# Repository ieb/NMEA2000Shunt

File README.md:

# Nmea2000 Battery Sensor.

Mk1 used the ADC on an Attiny3224. Fine for voltage but not really accurate enough for low levels of current on a 75mV 100A shunt. 

This version is built arround a INA219 which is far easier to use. It speaks CAN to communicate with a NMEA2000 bus.

A BLE version was created, but in the end I felt it was overcomplicated and would need to deep sleep to avoid draining the battery.

A Modbus version was also created, but since it adds annother bus I decided to rebuild as a NMEA2000 device using the SmallNMEA2000 library that was used in the CanPressure sensor and EngineManagement modules. Both have been in service for 2 years with no issues.

# megaTinyCore 

This code needs megaTiny core 2.6.4 to work as there are some timing bugs that cause it to fail with the default platform IO 2.5.11 version. Upgrading is a pain as it requires installing a custom package. Installs from github fail as the layout of the source repo is wrong and missing files. 

The hacky way is to install manually as its not possible to install from a git repo due to a bug in the pio code that parses versions numbers.

		cd ~/src
		git clone https://github.com/SpenceKonde/megaTinyCore.git
		cd megaTinyCore
		git co -b 2.6.4
		mkdir ~/.platformio/packages/framework-arduino-megaavr-megatinycore@2.6.4
		cd ~/.platformio/packages/framework-arduino-megaavr-megatinycore@2.6.4
		cat << EOF > .piopm
		{"type": "tool", "name": "framework-arduino-megaavr-megatinycore", "version": "2.6.4", "spec": {"owner": "platformio", "id": 11448, "name": "framework-arduino-megaavr-megatinycore", "requirements": null, "uri": null}}
		EOF
		cat << EOF > package.json
		{
		  "name": "framework-arduino-megaavr-megatinycore",
		  "version": "2.6.4",
		  "description": "Arduino Wiring-based Framework for Microchip tinyAVR 0-series and 1-series chips (megaTinyCore)",
		  "keywords": [
		    "framework",
		    "arduino",
		    "microchip",
		    "tinyAVR"
		  ],
		  "repository": {
		    "type": "git",
		    "url": "https://github.com/ieb/megaTinyCore"
		  }
		}
		EOF
		ln -s ~/megaTinyCore/megaavr/* .
		ln -s ~/megaTinyCore/ChangeLog.md .
		ln -s ~/megaTinyCore/Installation.md .
		ln -s ~/megaTinyCore/MakeUPDIProgrammer.md .
		ln -s ~/megaTinyCore/README.md .
		ln -s ~/megaTinyCore/Wiring.md .

# Oled display

There is a i2c header but at this time the oled display was removed as it served minimal purpose and consumes more current.

# LED status

normal operation is on for 250ms, off for 6s. Error states are indetified by a number of 250ms flashes followed by on for 3s off for 3s.

## Key

* ^ == short flash 
* -3s- == 3s on for 3s
* _3s_ off for 3s. 
* Cycle repeats after 6s

|   flashes   | condition                                   |
|-------------|---------------------------------------------|
| ^           | normal                                      |
| ^^ -3s-     | INA219 chip failure                         |
| ^^^ -s3-    | Can bus not connected or failing to respond |
| ^^^^^ -s3-  | Both Can and INA219 failing                 |

# ToDo

* [x] Basic implementation, with CAN.
* [x] Average current and voltage over time period, eg 30s
* [ ] Test CAN using a CandelLite adapter.
* [x] Calibrate NTC sensors.
* [x] ~~Add 1.3 inch Oled display~~
* [x] ~~Implement current monitoring with auto scaling for different ranges using features of the INA219~~ Limited benefit see p21 Table 7
* [ ] design and make box

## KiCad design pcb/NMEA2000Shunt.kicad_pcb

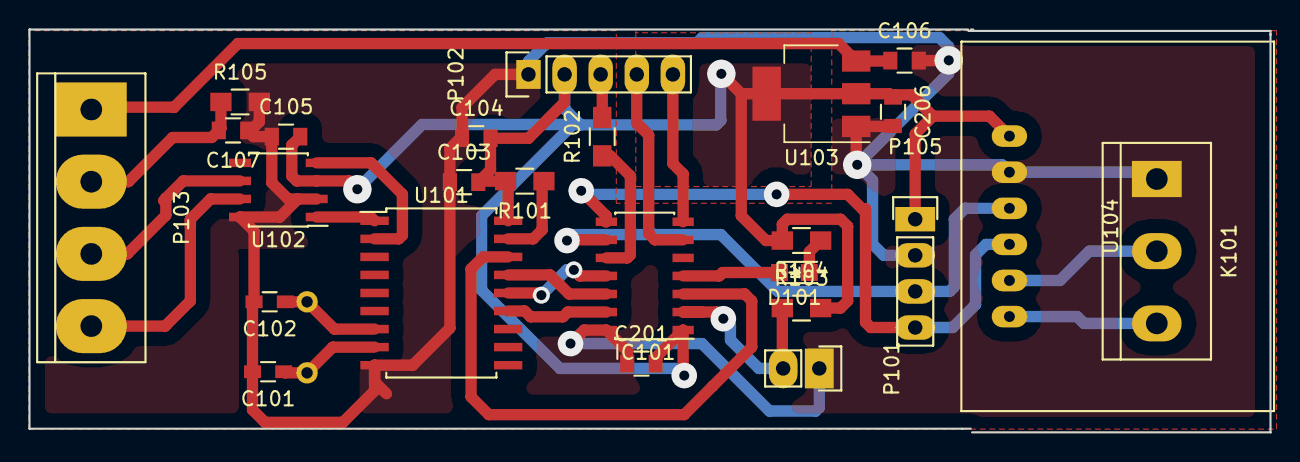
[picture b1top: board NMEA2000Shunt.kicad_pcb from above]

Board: 2 copper layers, 87.3 x 28.3 mm, 26 parts (1 on the bottom side), 26 nets.

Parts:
C101, C102: 22pF; R_0603_HandSoldering
C103, C106, C206: 10uF; C_0805
C104, C105, C107, C201: 100nF; C_0805
D101: LED; LED_0805
IC101: ATTINY3224-SS; SOIC-14_3.9x8.7mm_Pitch1.27mm
K101: Battery; bornier3
P101: Temp1; Pin_Header_Straight_1x02
P102: Prog; Pin_Header_Straight_1x05
P103: CAN; bornier4
P105: OLED; Pin_Header_Straight_1x04
R101, R103, R104, R105: 10K; R_0805_HandSoldering
R102: 270R; R_0805_HandSoldering
U101: MCP2515; SOIC-18W_7.5x11.6mm_Pitch1.27mm
U102: TJA1050; SOIC-8_3.9x4.9mm_Pitch1.27mm
U103: NCP1117ST50T3G; SOT-223-3Lead_TabPin2
U104: INA219-module; INA219Module
X101: 8MHz; Resonator-2pin_w10.0mm_h5.0mm

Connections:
5V: C103.2, C104.2, C105.2, C201.2, C206.1, IC101.1, P102.2, P105.1, R101.2, R103.2, R104.2, U101.18, U102.3, U103.2, U104.1
12v: C106.1, P103.1, U103.3
CANCS: IC101.3, U101.16
CANGND: C107.2, P103.2, R105.1
CANH: P103.4, U102.7
CANL: P103.3, U102.6
GND: C101.2, C102.2, C103.1, C104.1, C105.1, C106.2, C107.1, C201.1, C206.2, IC101.14, K101.1, P101.1, P102.1, P105.2, R105.2, U101.9, U102.2, U102.8, U103.1, U104.2
IN+: K101.3, U104.6
IN-: K101.2, U104.5
LED: D101.2, IC101.4
MISO: IC101.12, U101.15
MOSI: IC101.11, U101.14
unnamed: C101.1, U101.8, X101.1
unnamed: C102.1, U101.7, X101.2
unnamed: D101.1, R104.1
unnamed: P102.3, R102.2
unnamed: R101.1, U101.17
unnamed: U101.1, U102.1
unnamed: U101.2, U102.4
RX: IC101.6, P102.4
SCK: IC101.13, U101.13
SCL: IC101.9, P105.3, U104.3
SDA: IC101.8, P105.4, U104.4
TEMP1: IC101.2, P101.2, R103.1
TX: IC101.7, P102.5
UDPI: IC101.10, R102.1

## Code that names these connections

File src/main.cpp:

#include <Arduino.h>
#include <Wire.h>



#include "n2kshunt.h"
#include "commandline.h"
#include "ina219.h"
#include "config.h"
#include "ntcsensor.h"

// Hardware
// Vcc chip pin 1
#define TEMP1_PIN PIN_PA4 // chip pin 2
#define CANCS_PIN PIN_PA5 // chip pin 3
#define LED_PIN PIN_PA6 // chip pin 4
// PIN_PA7 not used       // chip pin 5
#define RX0_PIN   PIN_PB3 // chip pin 6, default
#define TX0_PIN   PIN_PB2 // chip pin 7, default
#define SDA_PIN   PIN_PB1 // chip pin 8, cant be moved.
#define SCL_PIN   PIN_PB0 // chip pin 9, cant be moved.
#define UDPI_PIN  PIN_PA0 // chip pin 10, cant be moved.
#define MOSI_PIN  PIN_PB1 // chip pin 11, default
#define MIS0_PIN  PIN_PB2 // chip pin 12, default
#define SCK_PIN   PIN_PB3 // chip pin 13, default
// GND chip pin 14

//  Check and update https://ieb.github.io/notes/ to get a clean address.
#define DEVICE_ADDRESS 26



// default serial for debug, serial 1 not used.
#define debug Serial


// configure CAN device
const SNMEA2000ProductInfo productInfomation PROGMEM={
                                       1300,                        // N2kVersion
                                       45,                         // Manufacturer's product code
                                       "Shunt",    // Manufacturer's Model ID
                                       "1.0.0.1 (2023-04-26)",     // Manufacturer's Software version code
                                       "1.0.0.2 (2023-04-26)",      // Manufacturer's Model version
                                       "0000003",                  // Manufacturer's Model serial code
                                       0,                           // SertificationLevel
                                       1                            // LoadEquivalency
};
const SNMEA2000ConfigInfo configInfo PROGMEM={
      "Battery Shunt",
      "Luna Technical Area",
      "https://github.com/ieb/NMEA2000Shunt"
};

uint8_t pgnEnableRegister = 0xff;


const unsigned long txPGN[] PROGMEM = { 
	127506L, // detailed DC status
	127513L, // battery configuration status
	127508L, // battery status message
    SNMEA200_DEFAULT_TX_PGN
};
const unsigned long rxPGN[] PROGMEM = { 
  SNMEA200_DEFAULT_RX_PGN
};

const SNMEA2000DeviceInfo devInfo = SNMEA2000DeviceInfo(
  02,   // device serial number
  170,  // Battery
  35    // Power
);



ConfigSettings settings;

Ina219 ina219(&debug);
CommandLine commandLine(&debug, &settings);
NtcSensor ntcSensor(&debug, TEMP1_PIN);


bool ina219Ok = false;
bool canOk = false;



N2kShunt n2kShunt = N2kShunt(DEVICE_ADDRESS, 
          &devInfo, 
          &productInfomation, 
          &configInfo, 
          &txPGN[0], 
          &rxPGN[0],
          CANCS_PIN
);
//          CANCS_PIN


void blink() {
	static unsigned long lastBlink = 0;
	static uint8_t led_state = 0;
	static unsigned long nextDelay = 3000;
	unsigned long now = millis();
	if ((now - lastBlink) > nextDelay ) {
		led_state = !led_state;
		digitalWrite(LED_PIN, led_state);
		if ( canOk && ina219Ok ) {
			if (!led_state) {
				// short bink dont block main thread.
				nextDelay = 250;
			} else {
				nextDelay = 6000;
			}
		} else if ( !led_state ) {
			nextDelay = 3000;
			// indicate a fault condition.
			// its ok to block the main thread as something is failing.
			// 3 flashes = can fail.
			// 2 flashes = ina219 fail.
			// 5 flashes == both failed.
			if (!canOk ) {
				for(int i = 0; i < 3; i++) {
					delay(250);
					digitalWrite(LED_PIN, HIGH);
					delay(250);
					digitalWrite(LED_PIN, LOW);
				}
			} 
			if (!ina219Ok) {
				for(int i = 0; i < 2; i++) {
					delay(250);
					digitalWrite(LED_PIN, HIGH);
					delay(250);
					digitalWrite(LED_PIN, LOW);
				}
			}
		    delay(250);
			digitalWrite(LED_PIN, HIGH);
		    delay(250);
			digitalWrite(LED_PIN, LOW);
		}
		lastBlink = millis();

	}

}



void readSensors() {
	debug.print(F(" v="));debug.print(ina219.getVoltage());
	debug.print(F(" mV c="));debug.print(ina219.getCurrent());
	double tempK = ntcSensor.getTemperature();
	debug.print(F(" A t="));debug.print(ntcSensor.getTemperature());
	debug.print(F(" K "));debug.print(ntcSensor.getTemperature()-273.15);
	debug.print(F(" C tons="));debug.print(millis());
	debug.println("");
}

void showStatus() {
	n2kShunt.dumpStatus();
}





void sendReading() {
	static unsigned long lastRead = 0;
	static uint8_t sid = 0;
	unsigned long now = millis();
	if ((now - lastRead) > 1500 ) {
		lastRead = now;
		sid++;
		double batteryTemperature = ntcSensor.getTemperature();
		double batteryVoltage = ina219.getVoltage();
		double batteryCurrent = ina219.getCurrent();
		n2kShunt.sendDCBatterStatusMessage(
			settings.config.batteryInstance,
			sid,
			batteryVoltage,
			batteryTemperature,
			batteryCurrent);
		// Not emitting Detailed DC battery status, as the calculations would almost certainly
		// be wrong. Better to rely on voltage and current and common sense.
	}
}

void sendBatteryConfigurationStatus() {
	static unsigned long lastSend = 0;
	unsigned long now = millis();
	if ((now - lastSend) > 15000 ) {
		lastSend = now;
		n2kShunt.sendBatteryConfigurationStatusMessage(
			NULL,
			settings.config.batteryInstance,
			settings.config.batteryType,
			settings.config.supportsEqualisation,
			settings.config.nominalVoltage,
			settings.config.batteryChemistry,
			settings.config.batteryCapacityAh * 3600.0,
			settings.config.batteryTemperatureCoeficient,
			settings.config.peukert,
			settings.config.chargeEfficiencyFactor);
	}		

}


bool isoRequestHandler(unsigned long requestedPGN, MessageHeader *messageHeader, byte * buffer, int len) {
	if ( requestedPGN == 127513L ) {
		n2kShunt.sendBatteryConfigurationStatusMessage(
			messageHeader,
			settings.config.batteryInstance,
			settings.config.batteryType,
			settings.config.supportsEqualisation,
			settings.config.nominalVoltage,
			settings.config.batteryChemistry,
			settings.config.batteryCapacityAh * 3600.0,
			settings.config.batteryTemperatureCoeficient,
			settings.config.peukert,
			settings.config.chargeEfficiencyFactor);		
		return true;
	}
	return false;
}





void setup() {

  // Open serial communications and wait for port to open:
  debug.begin(115200);

  pinMode(LED_PIN, OUTPUT);

  // try 115200, if that fails drop back to 9600 and set.

  debug.println(F("NMEA2000 Shunt - Booting....."));

  if ( ina219.begin() != I2C_OK) {
  	ina219Ok = false;
	debug.print(F("Failed to find INA219 chip, error:"));
	debug.println(ina219.getError());
 	debug.println(F("INA219 not responding"));
  } else {
  	ina219Ok = true;
  }

  commandLine.setCallbacks(&showStatus, &readSensors);
  commandLine.begin();




  commandLine.diagnosticsEnabled = false;


  debug.print(F("Shunt: "));
  debug.print(settings.config.shuntReading);
  debug.print(F("mV/"));
  debug.print(settings.config.shuntCurrent);
  debug.println(F("A"));
  ina219.setShutRange( settings.config.shuntReading, settings.config.shuntCurrent);

  debug.println(F("Opening CAN"));
  debug.print("CS Pin in main ");debug.println(CANCS_PIN);
  // only set on reboot.
  n2kShunt.setSerialNumber(settings.config.serialNumber);
  n2kShunt.setDeviceAddress(settings.config.deviceAddress);
  n2kShunt.setIsoRequestHandler(&isoRequestHandler);
  if ( !n2kShunt.open() ) {
  	canOk = false;
    debug.println(F("Failed to start NMEA2000, retry in 5s"));
    delay(5000);
  } else {
  	canOk = true;
  }
  debug.println(F("Opened, MCP2515 Operational"));
  debug.println(F("Running..."));
  debug.println(F("Press h for help menu"));


}




void loop() {
  static bool diagnosticsEnabled = false;
  
  if ( !canOk ) {
  	canOk = n2kShunt.open();
  };
  blink();
  sendReading();
  sendBatteryConfigurationStatus();
  n2kShunt.processMessages();
  if ( commandLine.checkCommand() ) {
  	if (!diagnosticsEnabled ) {
	  	n2kShunt.setDiagnostics(true);
	  	ina219.setDiagnostics(true);
	  	ntcSensor.setDiagnostics(true);
		diagnosticsEnabled = true;  		
  	}
  } else {
  	if ( diagnosticsEnabled ) {
	  	n2kShunt.setDiagnostics(false);
	  	ina219.setDiagnostics(false);
	  	ntcSensor.setDiagnostics(false);
		diagnosticsEnabled = false;  		
  	}

  }
}

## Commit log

2023-05-04 Initial Commit, working, can not tested
2023-05-07 Working version tested with Cansocket and canboat
2023-09-09 Fixed 49day overflows
